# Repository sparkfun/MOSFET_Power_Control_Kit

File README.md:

SparkFun MOSFET Power Control Kit
===================================

[*SparkFun MOSFET Power Control Kit (COM-12959)*](https://www.sparkfun.com/products/12959)

This is the SparkFun MOSFET Power Control Kit, a breakout PTH soldering kit for for the RFP30N06LE N-Channel MOSFET.
What we really like about this particular MOSFET is that it’s very common and offers very low on-resistance with a control 
(gate) voltage that is compatible with any 3-5V microcontroller or mechanical switch. This allows you to control high-power
 devices with very low-power control mechanisms.
 
 Repository Contents
-------------------
* **/Hardware** - All Eagle design files (.brd, .sch)

Product Versions
----------------
* [COM-10256](https://www.sparkfun.com/products/retired/10256)- Version 1.0. Retired. 

License Information
-------------------
The hardware is released under [Creative Commons ShareAlike 4.0 International](https://creativecommons.org/licenses/by-sa/4.0/).

Distributed as-is; no warranty is given.

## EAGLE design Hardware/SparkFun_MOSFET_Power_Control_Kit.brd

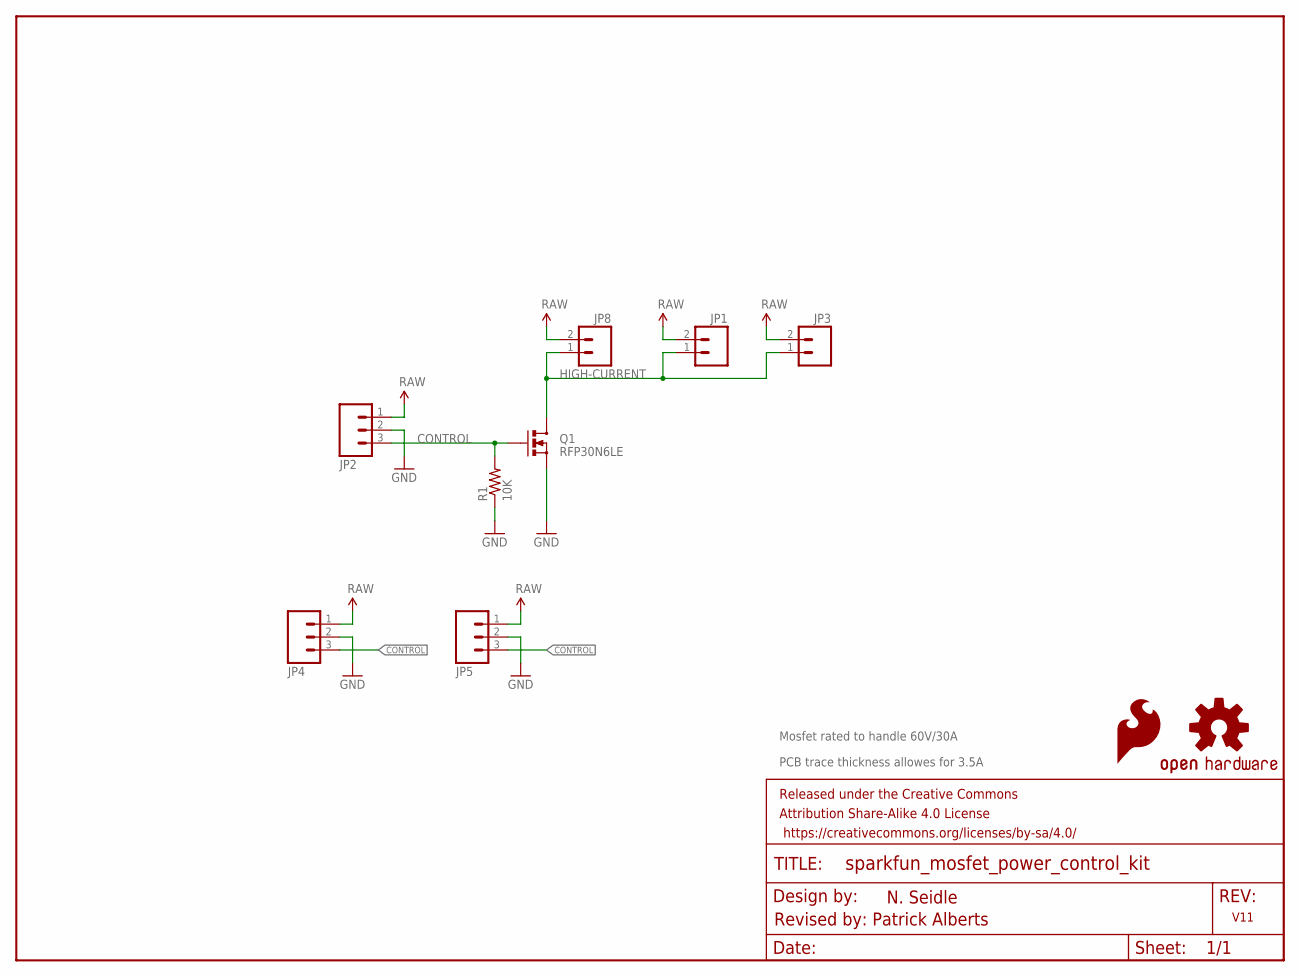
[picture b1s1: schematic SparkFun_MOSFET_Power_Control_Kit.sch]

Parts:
FRAME1: FRAME-LETTER; CREATIVE_COMMONS
JP1: M023.5MM; SCREWTERMINAL-3.5MM-2
JP2: M03JST-PTH; JST-3-PTH
JP3: M02PTH; 1X02
JP4: M03SCREW; SCREWTERMINAL-3.5MM-3
JP5: M03PTH; 1X03
JP8: M02JST-PTH-2; JST-2-PTH
LOGO1: OSHW-LOGOS; OSHW-LOGO-S
LOGO2: SFE_LOGO_FLAME.1_INCH; SFE_LOGO_FLAME_.1
Q1: RFP30N6LE; TO220V
R1: 10K; AXIAL-0.3

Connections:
CONTROL: JP2.3, JP4.3, JP5.3, Q1.1 (G), R1.P$2 (2)
GND: JP2.2, JP4.2, JP5.2, Q1.3 (S), R1.P$1 (1)
HIGH-CURRENT: JP1.1, JP3.1, JP8.1, Q1.2 (D)
VCC: JP1.2, JP2.1, JP3.2, JP4.1, JP5.1, JP8.2

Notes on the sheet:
N. Seidle
Revised by: Patrick Alberts
V11
Mosfet rated to handle 60V/30A
PCB trace thickness allowes for 3.5A

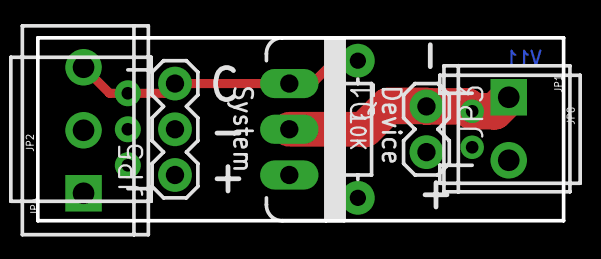
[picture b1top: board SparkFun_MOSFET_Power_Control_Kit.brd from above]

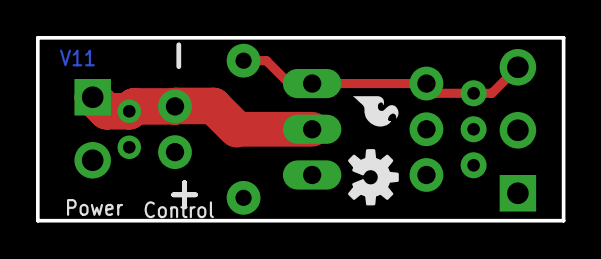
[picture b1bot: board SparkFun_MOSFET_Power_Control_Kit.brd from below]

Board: 2 copper layers, 29.2 x 10.2 mm, 11 parts (2 on the bottom side), 4 nets.

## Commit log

2014-07-07 Int commit with brd/sch
2014-08-04 Added extra headers, minor trace redo, sch work
2014-09-22 Silk Change
2014-12-03 Added measurements and version #
2014-12-04 Qc checklist fixes
    Added max current / voltage to sch
    fixed airwire
2014-12-05 More qc checklist changes
2015-03-02 Updating README with new part info, adding .gitignore
2015-03-02 Fixing README typo

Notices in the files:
parts and their libraries:
SparkFun-Connectors: Licensing: Creative Commons ShareAlike 4.0 International - https://creativecommons.org/licenses/by-sa/4.0
SparkFun-Aesthetics: Released under the Creative Commons Attribution Share-Alike 4.0 License
SparkFun-Aesthetics: Released under the Creative Commons
